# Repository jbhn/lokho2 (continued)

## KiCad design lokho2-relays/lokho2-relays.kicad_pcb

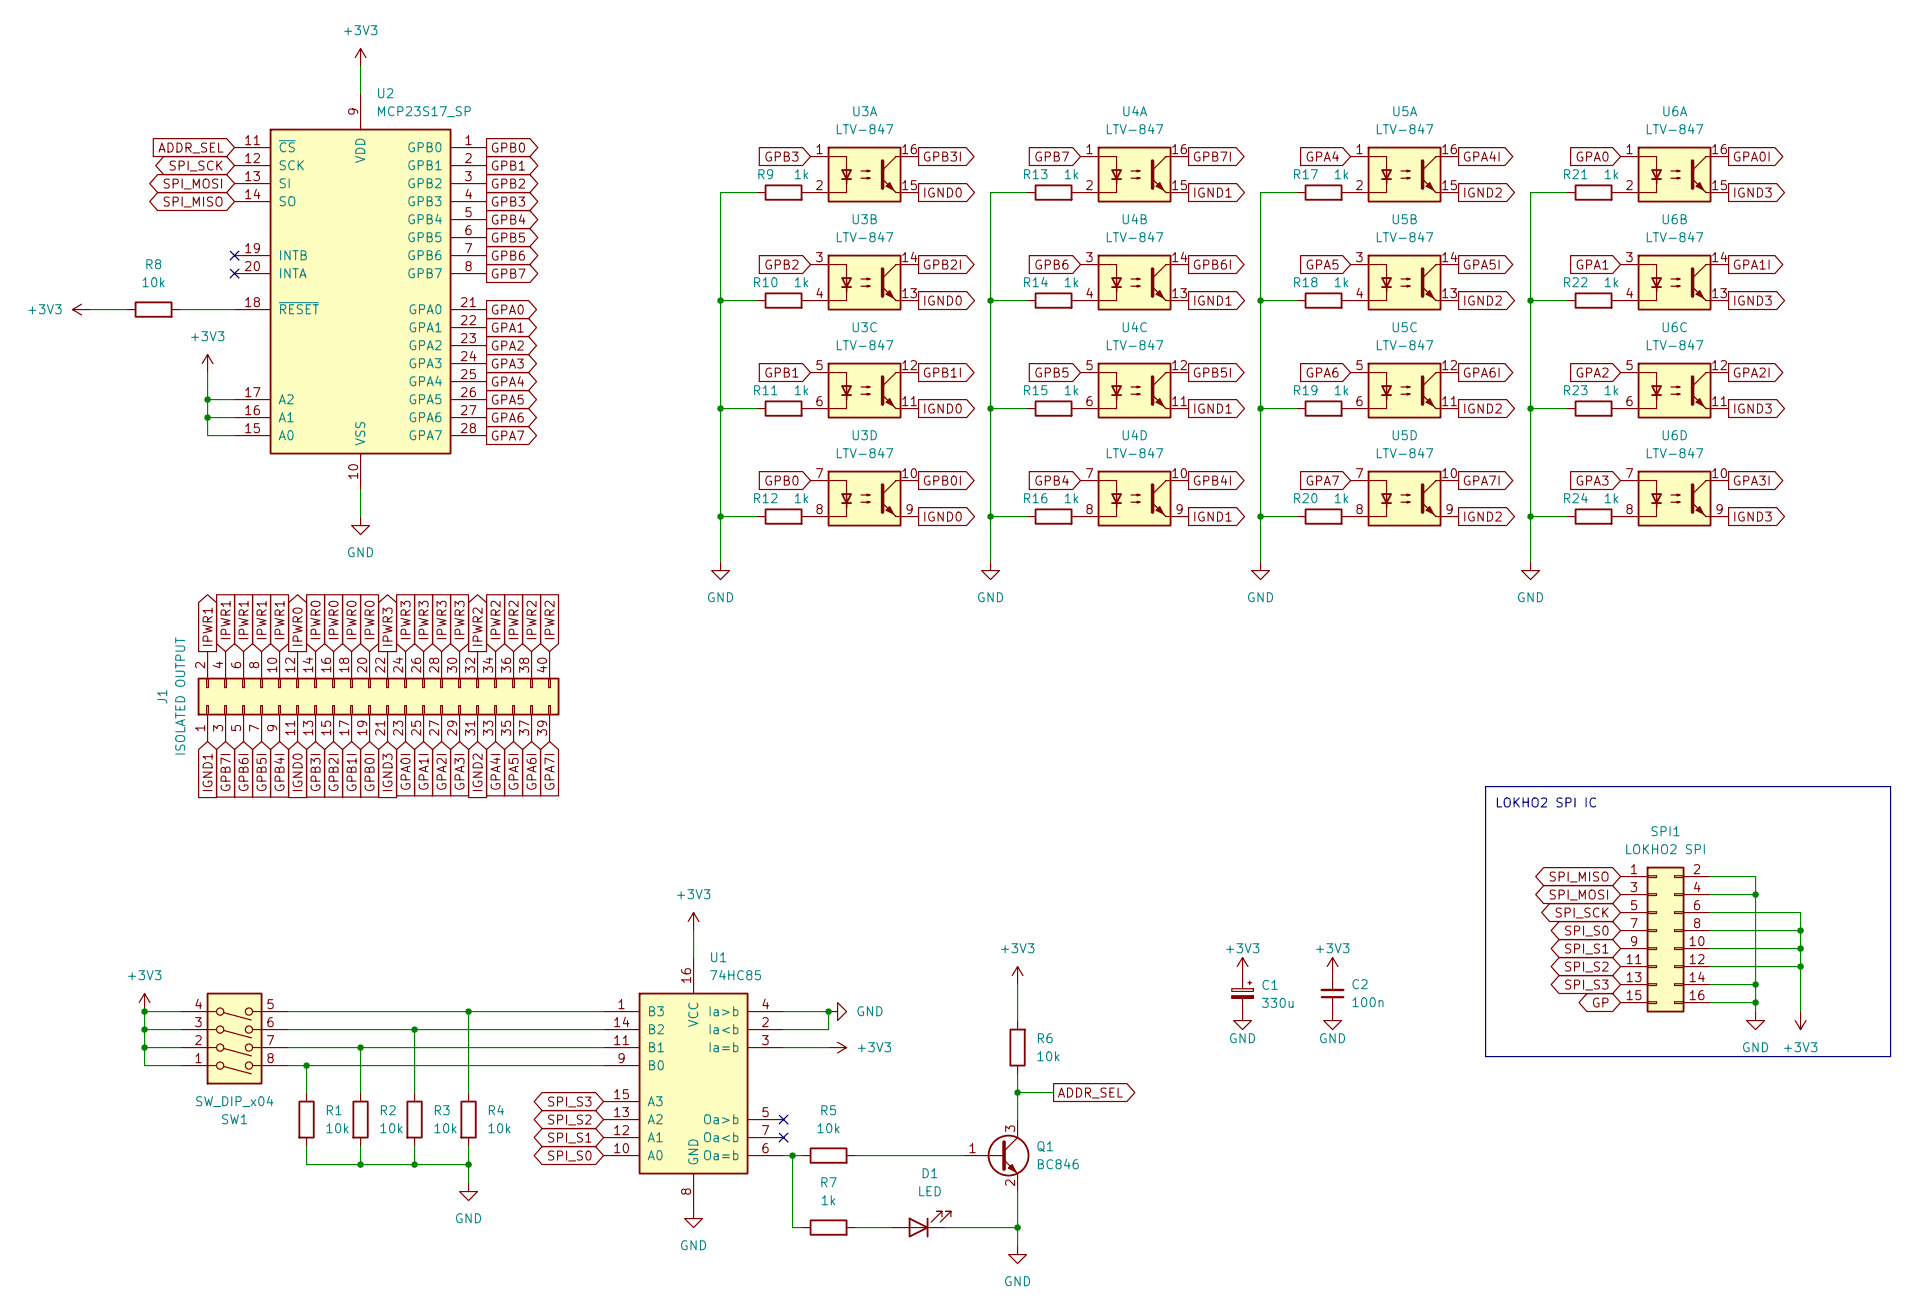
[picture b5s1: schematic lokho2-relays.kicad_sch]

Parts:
C1: 330u; CP_Radial_D8.0mm_P3.50mm
C2: 100n; C_Disc_D5.0mm_W2.5mm_P5.00mm
D1: LED; LED_D3.0mm
J1: ISOLATED OUTPUT; IDC-Header_2x20_P2.54mm_Horizontal
Q1: BC846; SOT-23
R1, R2, R3, R4, R5, R6, R8: 10k; R_Axial_DIN0204_L3.6mm_D1.6mm_P7.62mm_Horizontal
R7, R9, R10, R11, R12, R13, R14, R15, R16, R17, R18, R19, R20, R21, R22, R23, R24: 1k; R_Axial_DIN0204_L3.6mm_D1.6mm_P7.62mm_Horizontal
SPI1: LOKHO2 SPI; IDC-Header_2x08_P2.54mm_Horizontal
SW1: SW_DIP_x04; SW_DIP_SPSTx04_Slide_6.7x11.72mm_W7.62mm_P2.54mm_LowProfile
U1: 74HC85; SO-16_3.9x9.9mm_P1.27mm
U2: MCP23S17_SP; DIP-28_W7.62mm
U3, U4, U5, U6: LTV-847; DIP-16_W7.62mm

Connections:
+3V3: C1.1, C2.2, R6.2, R8.1, SPI1.6, SPI1.8, SPI1.10, SPI1.12, SW1.1, SW1.2, SW1.3, SW1.4, U1.3 (Ia=b), U1.16 (VCC), U2.9 (VDD), U2.15 (A0), U2.16 (A1), U2.17 (A2)
ADDR_SEL: Q1.3 (C), R6.1, U2.11 (~CS)
GND: C1.2, C2.1, D1.1 (K), Q1.2 (E), R1.2, R2.2, R3.2, R4.2, R9.1, R10.1, R11.1, R12.1, R13.1, R14.1, R15.1, R16.1, R17.1, R18.1, R19.1, R20.1, R21.1, R22.1, R23.1, R24.1, SPI1.2, SPI1.4, SPI1.14, SPI1.16, U1.2 (Ia<b), U1.4 (Ia>b), U1.8 (GND), U2.10 (VSS)
GP: SPI1.15
GPA0: U2.21 (GPA0), U6.1
GPA0I: J1.23, U6.16
GPA1: U2.22 (GPA1), U6.3
GPA1I: J1.25, U6.14
GPA2: U2.23 (GPA2), U6.5
GPA2I: J1.27, U6.12
GPA3: U2.24 (GPA3), U6.7
GPA3I: J1.29, U6.10
GPA4: U2.25 (GPA4), U5.1
GPA4I: J1.33, U5.16
GPA5: U2.26 (GPA5), U5.3
GPA5I: J1.35, U5.14
GPA6: U2.27 (GPA6), U5.5
GPA6I: J1.37, U5.12
GPA7: U2.28 (GPA7), U5.7
GPA7I: J1.39, U5.10
GPB0: U2.1 (GPB0), U3.7
GPB0I: J1.19, U3.10
GPB1: U2.2 (GPB1), U3.5
GPB1I: J1.17, U3.12
GPB2: U2.3 (GPB2), U3.3
GPB2I: J1.15, U3.14
GPB3: U2.4 (GPB3), U3.1
GPB3I: J1.13, U3.16
GPB4: U2.5 (GPB4), U4.7
GPB4I: J1.9, U4.10
GPB5: U2.6 (GPB5), U4.5
GPB5I: J1.7, U4.12
GPB6: U2.7 (GPB6), U4.3
GPB6I: J1.5, U4.14
GPB7: U2.8 (GPB7), U4.1
GPB7I: J1.3, U4.16
IGND0: J1.11, U3.9, U3.11, U3.13, U3.15
IGND1: J1.1, U4.9, U4.11, U4.13, U4.15
IGND2: J1.31, U5.9, U5.11, U5.13, U5.15
IGND3: J1.21, U6.9, U6.11, U6.13, U6.15
IPWR0: J1.12, J1.14, J1.16, J1.18, J1.20
IPWR1: J1.2, J1.4, J1.6, J1.8, J1.10
IPWR2: J1.32, J1.34, J1.36, J1.38, J1.40
IPWR3: J1.22, J1.24, J1.26, J1.28, J1.30
unnamed: D1.2 (A), R7.2
unnamed: Q1.1 (B), R5.2
unnamed: R9.2, U3.2
unnamed: R10.2, U3.4
unnamed: R11.2, U3.6
unnamed: R12.2, U3.8
unnamed: R13.2, U4.2
unnamed: R14.2, U4.4
unnamed: R15.2, U4.6
unnamed: R16.2, U4.8
unnamed: R17.2, U5.2
unnamed: R18.2, U5.4
unnamed: R19.2, U5.6
unnamed: R20.2, U5.8
unnamed: R21.2, U6.2
unnamed: R22.2, U6.4
unnamed: R23.2, U6.6
unnamed: R24.2, U6.8
unnamed: R1.1, SW1.8, U1.9 (B0)
unnamed: R2.1, SW1.7, U1.11 (B1)
unnamed: R3.1, SW1.6, U1.14 (B2)
unnamed: R4.1, SW1.5, U1.1 (B3)
unnamed: R5.1, R7.1, U1.6 (Oa=b)
unnamed: R8.2, U2.18 (~RESET)
SPI_MISO: SPI1.1, U2.14 (SO)
SPI_MOSI: SPI1.3, U2.13 (SI)
SPI_S0: SPI1.7, U1.10 (A0)
SPI_S1: SPI1.9, U1.12 (A1)
SPI_S2: SPI1.11, U1.13 (A2)
SPI_S3: SPI1.13, U1.15 (A3)
SPI_SCK: SPI1.5, U2.12 (SCK)

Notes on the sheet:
LOKHO2 SPI IC

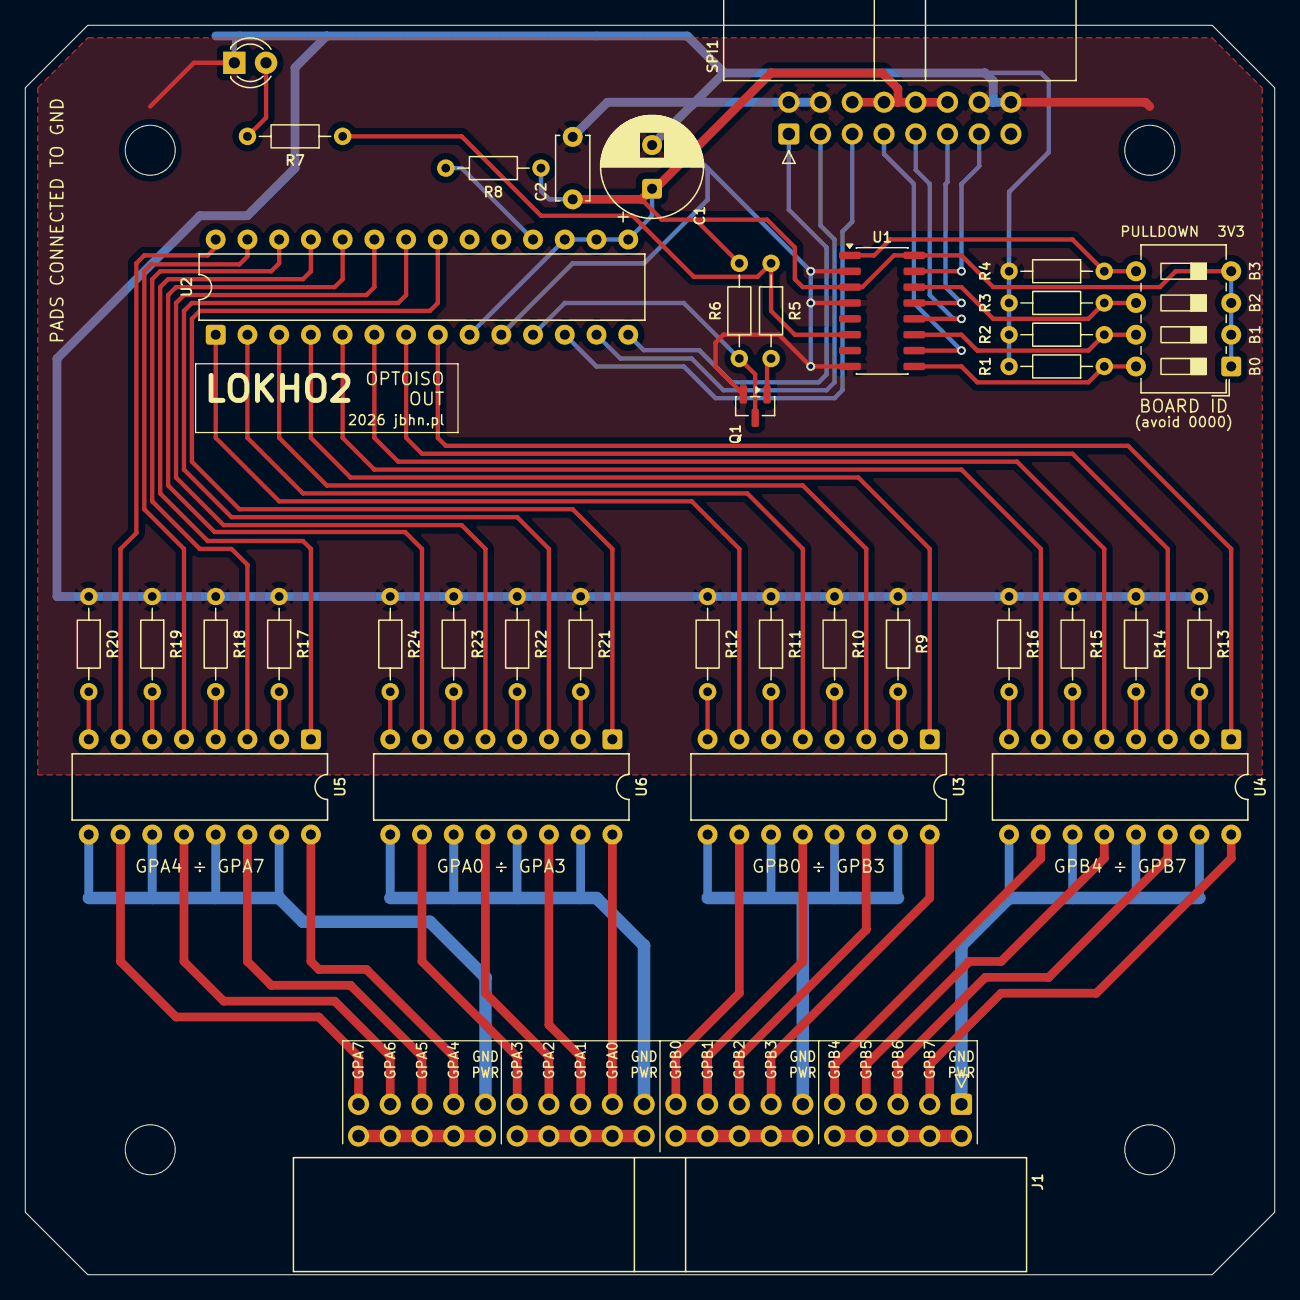
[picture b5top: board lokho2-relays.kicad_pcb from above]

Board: 2 copper layers, 100.0 x 100.0 mm, 37 parts (0 on the bottom side), 74 nets.

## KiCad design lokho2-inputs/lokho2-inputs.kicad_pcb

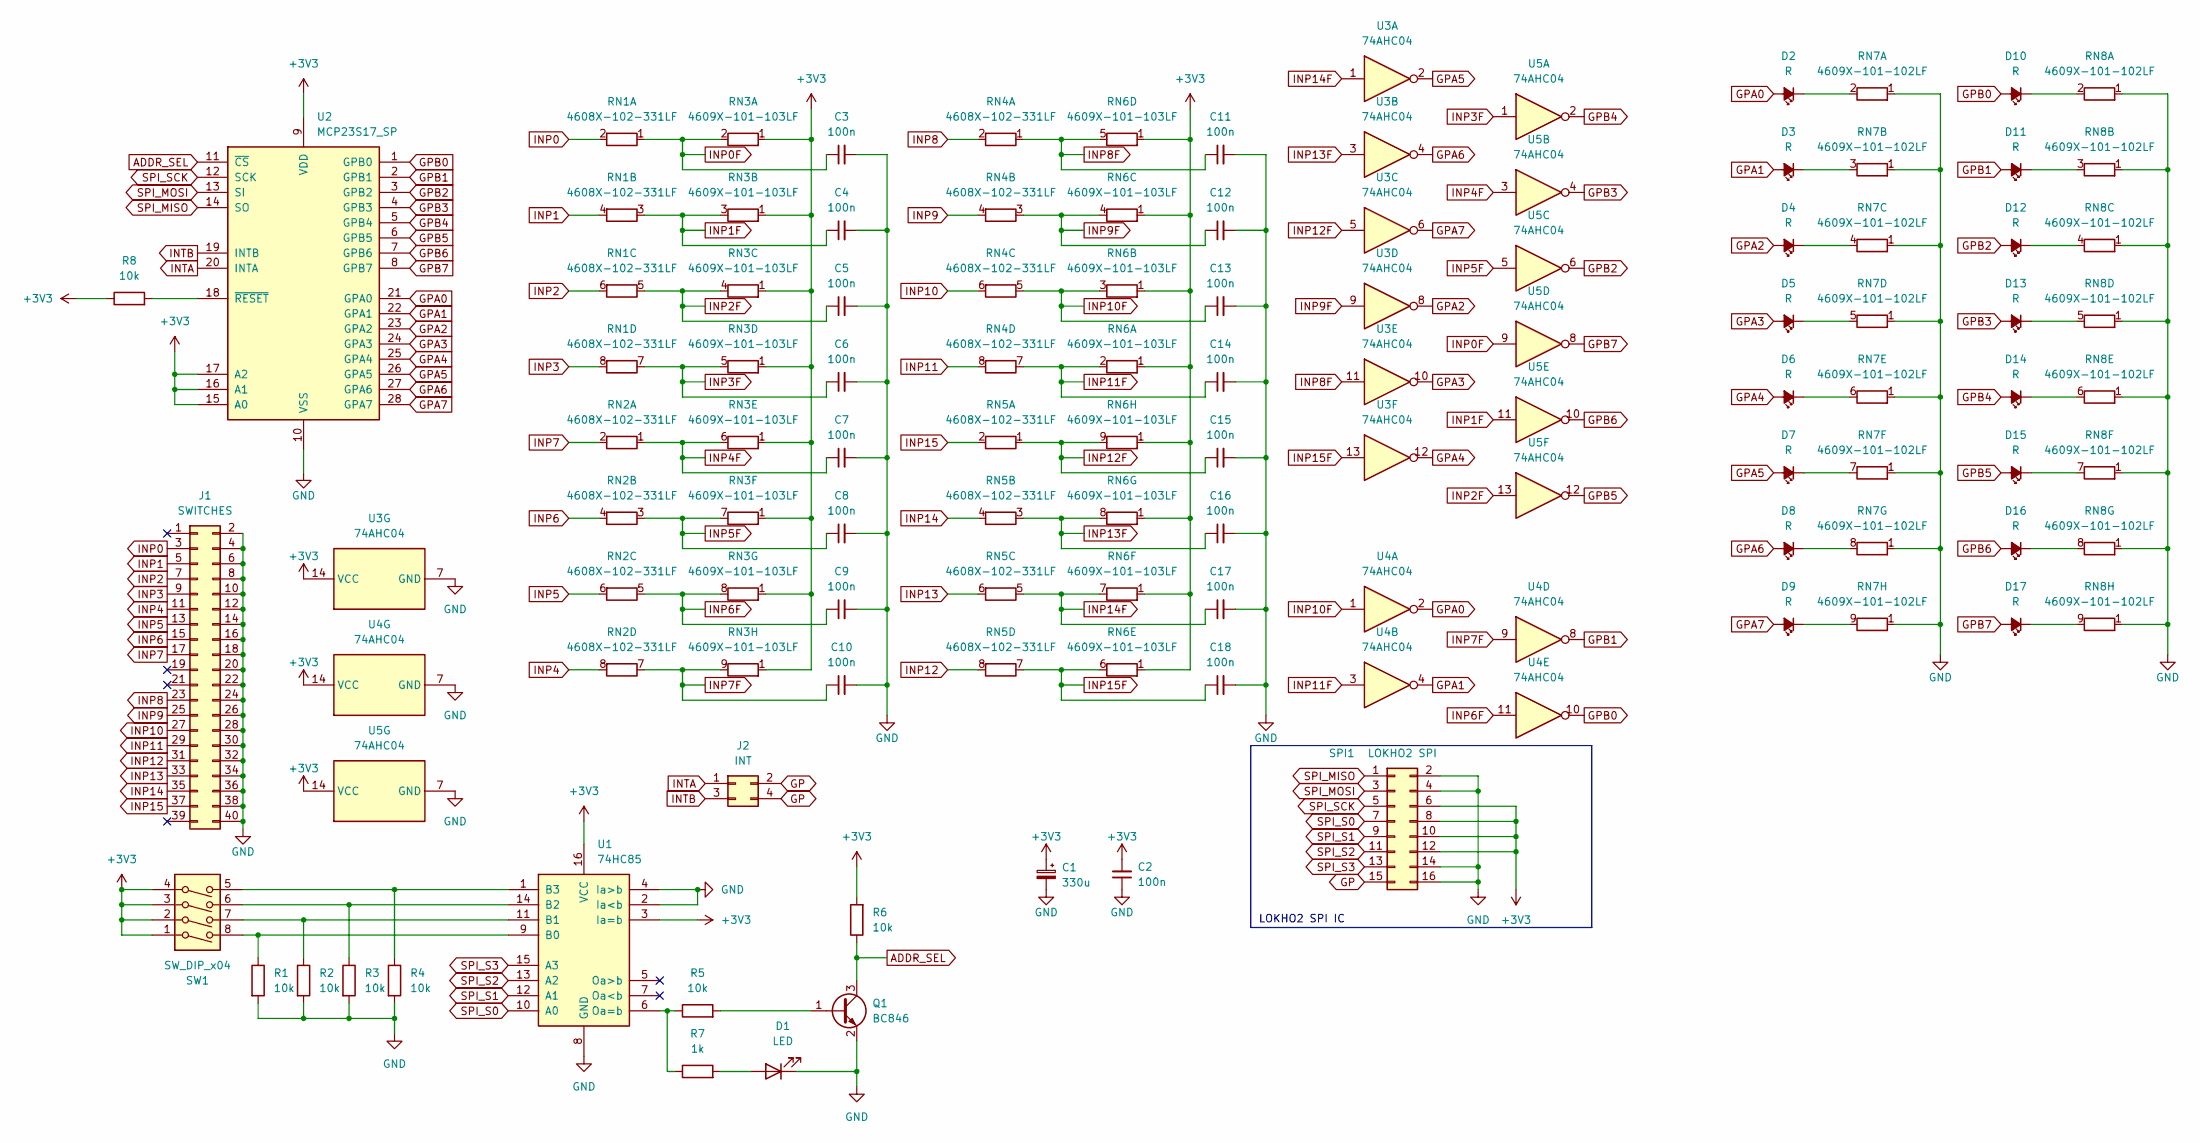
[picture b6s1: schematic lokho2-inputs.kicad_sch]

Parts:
C1: 330u; CP_Radial_D8.0mm_P3.50mm
C2: 100n; C_Disc_D5.0mm_W2.5mm_P5.00mm
C3, C4, C5, C6, C7, C8, C9, C10, C11, C12, C13, C14, C15, C16, C17, C18: 100n; C_Disc_D4.3mm_W1.9mm_P5.00mm
D1: LED; LED_D3.0mm
D2, D3, D4, D5, D6, D7, D8, D9, D10, D11, D12, D13, D14, D15, D16, D17: R; LED_1206_3216Metric_Pad1.42x1.75mm_HandSolder
J1: SWITCHES; IDC-Header_2x20_P2.54mm_Horizontal
J2: INT; PinHeader_2x02_P2.54mm_Vertical
Q1: BC846; SOT-23
R1, R2, R3, R4, R5, R6, R8: 10k; R_Axial_DIN0204_L3.6mm_D1.6mm_P7.62mm_Horizontal
R7: 1k; R_Axial_DIN0204_L3.6mm_D1.6mm_P7.62mm_Horizontal
RN1, RN2, RN4, RN5: 4608X-102-331LF; R_Array_SIP8
RN3, RN6: 4609X-101-103LF; R_Array_SIP9
RN7, RN8: 4609X-101-102LF; R_Array_SIP9
SPI1: LOKHO2 SPI; IDC-Header_2x08_P2.54mm_Horizontal
SW1: SW_DIP_x04; SW_DIP_SPSTx04_Slide_6.7x11.72mm_W7.62mm_P2.54mm_LowProfile
U1: 74HC85; SO-16_3.9x9.9mm_P1.27mm
U2: MCP23S17_SP; DIP-28_W7.62mm
U3, U4, U5: 74AHC04; DIP-14_W7.62mm

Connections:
+3V3: C1.1, C2.2, R6.2, R8.1, RN3.1 (R1), RN6.1 (R1), SPI1.6, SPI1.8, SPI1.10, SPI1.12, SW1.1, SW1.2, SW1.3, SW1.4, U1.3 (Ia=b), U1.16 (VCC), U2.9 (VDD), U2.15 (A0), U2.16 (A1), U2.17 (A2), U3.14 (VCC), U4.14 (VCC), U5.14 (VCC)
ADDR_SEL: Q1.3 (C), R6.1, U2.11 (~CS)
GND: C1.2, C2.1, C3.2, C4.2, C5.2, C6.2, C7.2, C8.2, C9.2, C10.2, C11.2, C12.2, C13.2, C14.2, C15.2, C16.2, C17.2, C18.2, D1.1 (K), J1.2, J1.4, J1.6, J1.8, J1.10, J1.12, J1.14, J1.16, J1.18, J1.20, J1.22, J1.24, J1.26, J1.28, J1.30, J1.32, J1.34, J1.36, J1.38, J1.40, Q1.2 (E), R1.2, R2.2, R3.2, R4.2, RN7.1 (R1), RN8.1 (R1), SPI1.2, SPI1.4, SPI1.14, SPI1.16, U1.2 (Ia<b), U1.4 (Ia>b), U1.8 (GND), U2.10 (VSS), U3.7 (GND), U4.7 (GND), U5.7 (GND)
GP: J2.2, J2.4, SPI1.15
GPA0: D2.2 (A), U2.21 (GPA0), U4.2
GPA1: D3.2 (A), U2.22 (GPA1), U4.4
GPA2: D4.2 (A), U2.23 (GPA2), U3.8
GPA3: D5.2 (A), U2.24 (GPA3), U3.10
GPA4: D6.2 (A), U2.25 (GPA4), U3.12
GPA5: D7.2 (A), U2.26 (GPA5), U3.2
GPA6: D8.2 (A), U2.27 (GPA6), U3.4
GPA7: D9.2 (A), U2.28 (GPA7), U3.6
GPB0: D10.2 (A), U2.1 (GPB0), U4.10
GPB1: D11.2 (A), U2.2 (GPB1), U4.8
GPB2: D12.2 (A), U2.3 (GPB2), U5.6
GPB3: D13.2 (A), U2.4 (GPB3), U5.4
GPB4: D14.2 (A), U2.5 (GPB4), U5.2
GPB5: D15.2 (A), U2.6 (GPB5), U5.12
GPB6: D16.2 (A), U2.7 (GPB6), U5.10
GPB7: D17.2 (A), U2.8 (GPB7), U5.8
INP0: J1.3, RN1.2 (R1.2)
INP0F: C3.1, RN1.1 (R1.1), RN3.2 (R1.2), U5.9
INP1: J1.5, RN1.4 (R2.2)
INP1F: C4.1, RN1.3 (R2.1), RN3.3 (R2.2), U5.11
INP2: J1.7, RN1.6 (R3.2)
INP2F: C5.1, RN1.5 (R3.1), RN3.4 (R3.2), U5.13
INP3: J1.9, RN1.8 (R4.2)
INP3F: C6.1, RN1.7 (R4.1), RN3.5 (R4.2), U5.1
INP4: J1.11, RN2.8 (R4.2)
INP4F: C7.1, RN2.1 (R1.1), RN3.6 (R5.2), U5.3
INP5: J1.13, RN2.6 (R3.2)
INP5F: C8.1, RN2.3 (R2.1), RN3.7 (R6.2), U5.5
INP6: J1.15, RN2.4 (R2.2)
INP6F: C9.1, RN2.5 (R3.1), RN3.8 (R7.2), U4.11
INP7: J1.17, RN2.2 (R1.2)
INP7F: C10.1, RN2.7 (R4.1), RN3.9 (R8.2), U4.9
INP8: J1.23, RN4.2 (R1.2)
INP8F: C11.1, RN4.1 (R1.1), RN6.5 (R4.2), U3.11
INP9: J1.25, RN4.4 (R2.2)
INP9F: C12.1, RN4.3 (R2.1), RN6.4 (R3.2), U3.9
INP10: J1.27, RN4.6 (R3.2)
INP10F: C13.1, RN4.5 (R3.1), RN6.3 (R2.2), U4.1
INP11: J1.29, RN4.8 (R4.2)
INP11F: C14.1, RN4.7 (R4.1), RN6.2 (R1.2), U4.3
INP12: J1.31, RN5.8 (R4.2)
INP12F: C15.1, RN5.1 (R1.1), RN6.9 (R8.2), U3.5
INP13: J1.33, RN5.6 (R3.2)
INP13F: C16.1, RN5.3 (R2.1), RN6.8 (R7.2), U3.3
INP14: J1.35, RN5.4 (R2.2)
INP14F: C17.1, RN5.5 (R3.1), RN6.7 (R6.2), U3.1
INP15: J1.37, RN5.2 (R1.2)
INP15F: C18.1, RN5.7 (R4.1), RN6.6 (R5.2), U3.13
INTA: J2.1, U2.20 (INTA)
INTB: J2.3, U2.19 (INTB)
unnamed: D1.2 (A), R7.2
unnamed: D2.1 (K), RN7.2 (R1.2)
unnamed: D3.1 (K), RN7.3 (R2.2)
unnamed: D4.1 (K), RN7.4 (R3.2)
unnamed: D5.1 (K), RN7.5 (R4.2)
unnamed: D6.1 (K), RN7.6 (R5.2)
unnamed: D7.1 (K), RN7.7 (R6.2)
unnamed: D8.1 (K), RN7.8 (R7.2)
unnamed: D9.1 (K), RN7.9 (R8.2)
unnamed: D10.1 (K), RN8.2 (R1.2)
unnamed: D11.1 (K), RN8.3 (R2.2)
unnamed: D12.1 (K), RN8.4 (R3.2)
unnamed: D13.1 (K), RN8.5 (R4.2)
unnamed: D14.1 (K), RN8.6 (R5.2)
unnamed: D15.1 (K), RN8.7 (R6.2)
unnamed: D16.1 (K), RN8.8 (R7.2)
unnamed: D17.1 (K), RN8.9 (R8.2)
unnamed: Q1.1 (B), R5.2
unnamed: R1.1, SW1.8, U1.9 (B0)
unnamed: R2.1, SW1.7, U1.11 (B1)
unnamed: R3.1, SW1.6, U1.14 (B2)
unnamed: R4.1, SW1.5, U1.1 (B3)
unnamed: R5.1, R7.1, U1.6 (Oa=b)
unnamed: R8.2, U2.18 (~RESET)
SPI_MISO: SPI1.1, U2.14 (SO)
SPI_MOSI: SPI1.3, U2.13 (SI)
SPI_S0: SPI1.7, U1.10 (A0)
SPI_S1: SPI1.9, U1.12 (A1)
SPI_S2: SPI1.11, U1.13 (A2)
SPI_S3: SPI1.13, U1.15 (A3)
SPI_SCK: SPI1.5, U2.12 (SCK)

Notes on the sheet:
LOKHO2 SPI IC

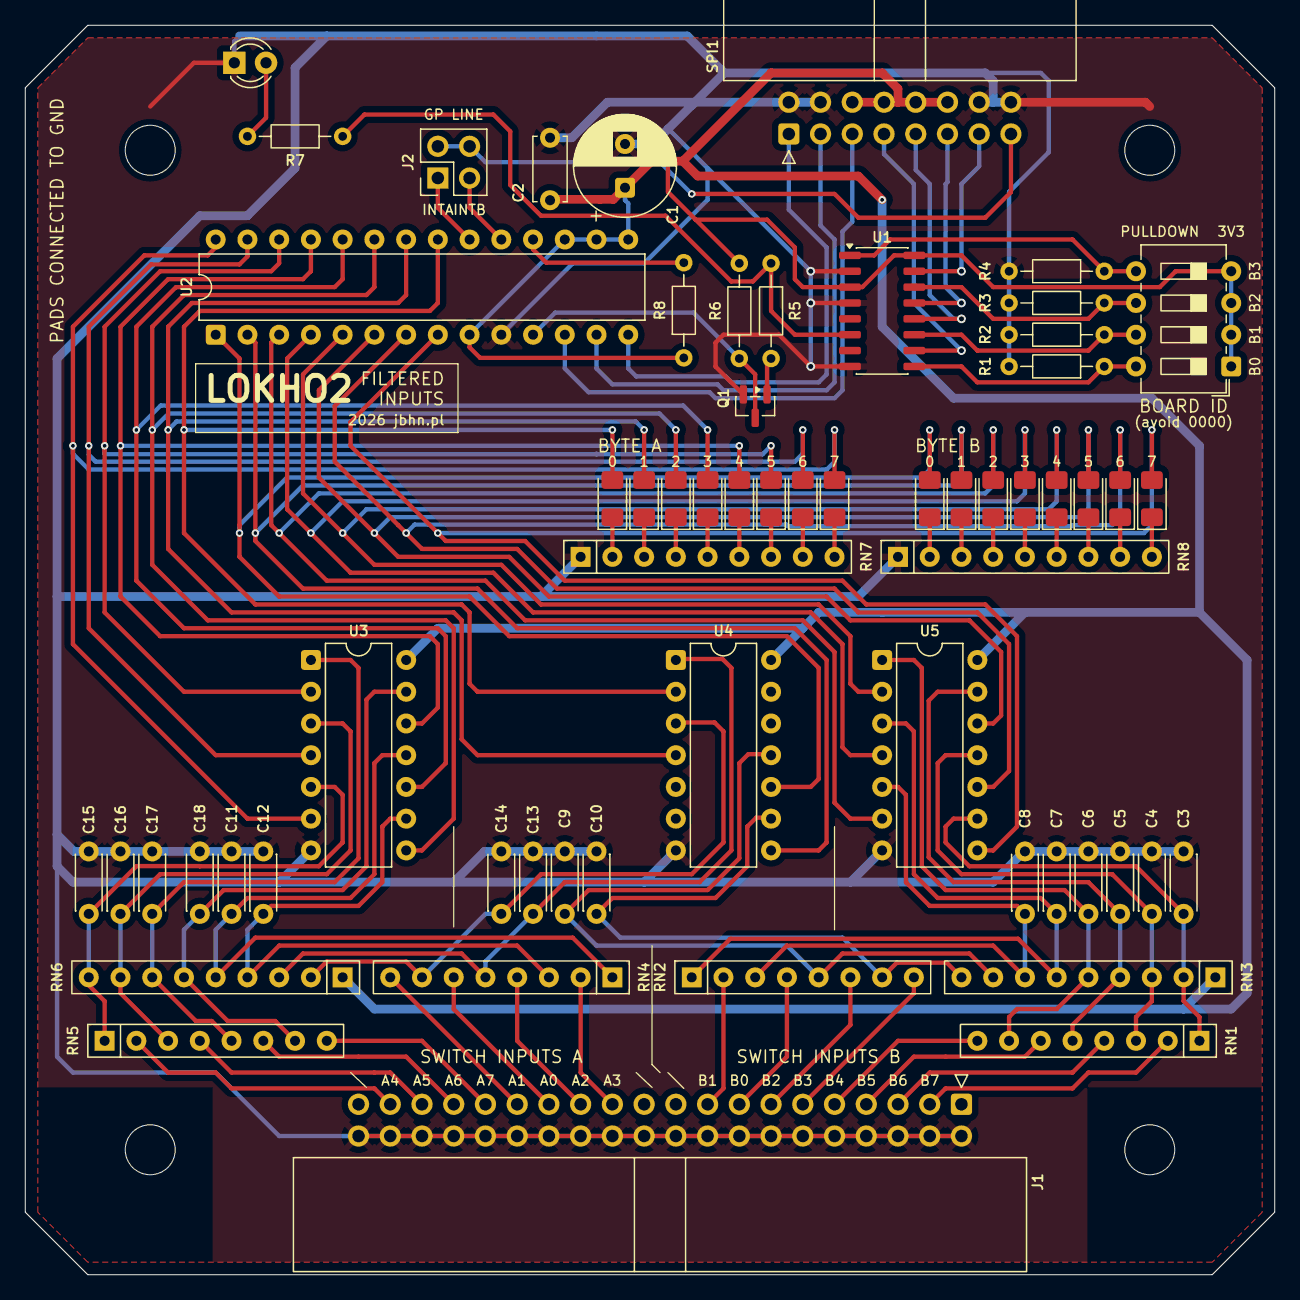
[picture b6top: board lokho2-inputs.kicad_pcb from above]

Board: 2 copper layers, 100.0 x 100.0 mm, 61 parts (0 on the bottom side), 85 nets.

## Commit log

2026-02-01 license
2026-02-03 added INT-GP connection option
2026-02-03 font unify
2026-02-03 production files
2026-02-03 pcb description
2026-02-03 .gitignore prod packs
